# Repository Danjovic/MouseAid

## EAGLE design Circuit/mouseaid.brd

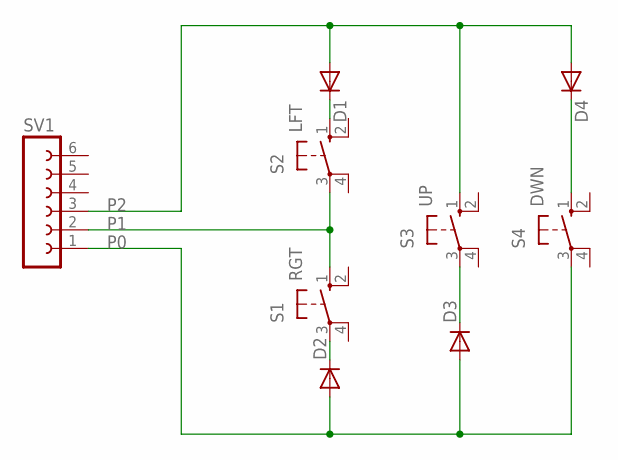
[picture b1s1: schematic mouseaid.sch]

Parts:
D1, D2, D3, D4: DIODE-D-7.5; D-7.5
S1: RGT; B3F-40XX
S2: LFT; B3F-40XX
S3: UP; B3F-40XX
S4: DWN; B3F-40XX
SV1: FE06W

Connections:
unnamed: D4.C, S4.1 (S)
unnamed: D1.C, S2.1 (S)
unnamed: D2.C, S1.3
unnamed: D3.C, S3.3
P0: D2.A, D3.A, S4.3, SV1.1
P1: S1.1 (S), S2.3, SV1.2
P2: D1.A, D4.A, S3.1 (S), SV1.3

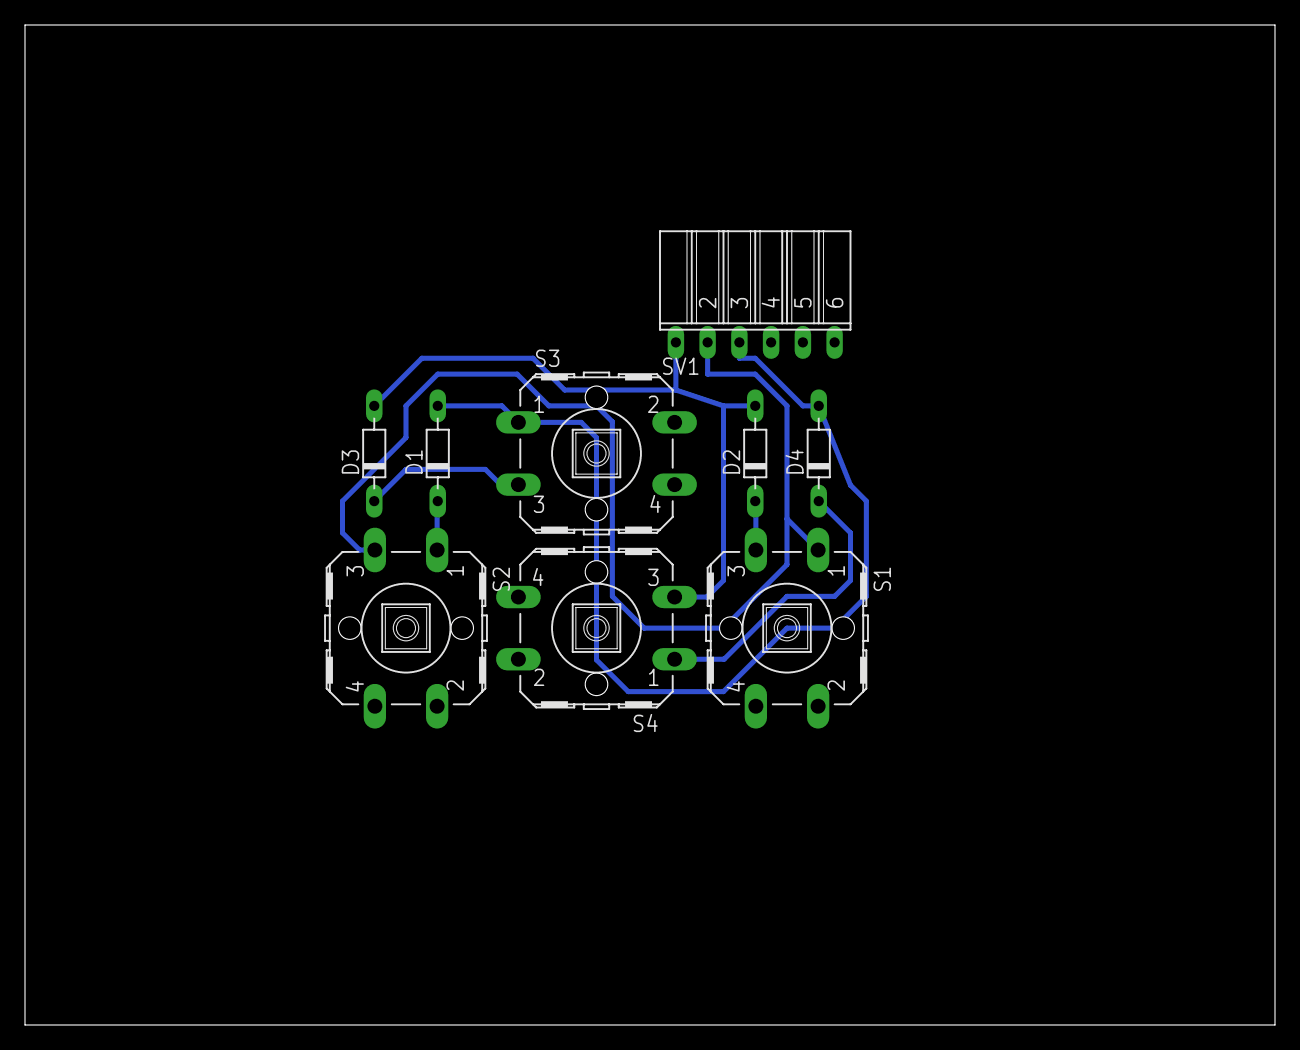
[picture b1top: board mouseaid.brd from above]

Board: 2 copper layers, 100.0 x 80.0 mm, 9 parts (0 on the bottom side), 7 nets.

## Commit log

2017-04-02 :tada: Added .gitattributes & .gitignore files
2017-04-02 Creation of repository
2017-04-02 Added sensitivity control
